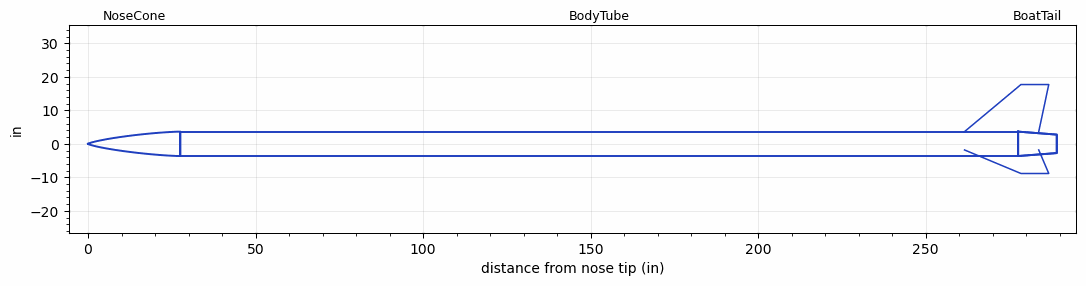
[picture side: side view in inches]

<RASAeroDocument>
 <FileVersion>2</FileVersion>
 <RocketDesign>
  <NoseCone>
   <Length>27.56</Length>
   <Diameter>7.283</Diameter>
   <Shape>Von Karman Ogive</Shape>
   <Location>0</Location>
  </NoseCone>
  <BodyTube>
   <Length>250</Length>
   <Diameter>7.283</Diameter>
   <Location>27.56</Location>
   <BoattailLength>11.532</BoattailLength>
   <BoattailRearDiameter>5.511</BoattailRearDiameter>
   <Overhang>6.146999</Overhang>
   <Fin>
    <Count>3</Count>
    <Chord>22.147</Chord>
    <Span>14.055</Span>
    <SweepDistance>16.84</SweepDistance>
    <TipChord>8.3</TipChord>
    <Thickness>0.2362</Thickness>
    <Location>16</Location>
    <AirfoilSection>Hexagonal</AirfoilSection>
    <FX1>1</FX1>
    <FX3>1</FX3>
   </Fin>
   <Protuberance>
    <StreamlinedNoBaseDrag>1.5</StreamlinedNoBaseDrag>
    <StreamlinedWithBaseDrag>1.94</StreamlinedWithBaseDrag>
    <InclinedPlate1Angle>0</InclinedPlate1Angle>
    <InclinedPlate1FrontalArea>0</InclinedPlate1FrontalArea>
    <InclinedPlate2Angle>0</InclinedPlate2Angle>
    <InclinedPlate2FrontalArea>0</InclinedPlate2FrontalArea>
   </Protuberance>
  </BodyTube>
  <BoatTail>
   <Length>11.532</Length>
   <Diameter>7.283</Diameter>
   <RearDiameter>5.511</RearDiameter>
   <Location>277.56</Location>
  </BoatTail>
  <Surface>Smooth Paint</Surface>
  <ModifiedBarrowman>False</ModifiedBarrowman>
  <Turbulence>False</Turbulence>
  <UseBooster1>False</UseBooster1>
  <UseBooster2>False</UseBooster2>
 </RocketDesign>
 <LaunchSite>
  <Altitude>0</Altitude>
  <Pressure>0</Pressure>
  <RodAngle>1</RodAngle>
  <RodLength>39</RodLength>
  <Temperature>74</Temperature>
  <WindSpeed>9.46</WindSpeed>
 </LaunchSite>
 <Recovery>
  <Altitude1>1000</Altitude1>
  <Altitude2>1500</Altitude2>
  <DeviceType1>Parachute</DeviceType1>
  <DeviceType2>Parachute</DeviceType2>
  <Event1>True</Event1>
  <Event2>True</Event2>
  <Size1>43</Size1>
  <Size2>120</Size2>
  <EventType1>Apogee</EventType1>
  <EventType2>Altitude</EventType2>
  <CD1>1.33</CD1>
  <CD2>1.33</CD2>
 </Recovery>
 <SimulationList>
  <Simulation>
   <SustainerEngine>RLFucked3  (ICLR)</SustainerEngine>
   <SustainerLaunchWt>280</SustainerLaunchWt>
   <SustainerNozzleDiameter>3.54</SustainerNozzleDiameter>
   <SustainerCG>200</SustainerCG>
   <SustainerIgnitionDelay>0</SustainerIgnitionDelay>
   <Booster1SeparationDelay>0</Booster1SeparationDelay>
   <Booster1IgnitionDelay>0</Booster1IgnitionDelay>
   <IncludeBooster1>False</IncludeBooster1>
   <Booster2Delay>0</Booster2Delay>
   <IncludeBooster2>False</IncludeBooster2>
   <TimetoApogee>105.7342</TimetoApogee>
   <MaxAltitude>160897.2</MaxAltitude>
   <MaxVelocity>3758.369</MaxVelocity>
  </Simulation>
 </SimulationList>
</RASAeroDocument>
